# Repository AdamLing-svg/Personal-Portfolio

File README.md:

# About
Third-year Aerospace Engineering student at Toronto Metropolitan University (spacecraft stream), focused on mechanical subsystem design, avionics, and aircraft performance. This repo collects technical reports, design work, and code from coursework and design teams.
---

# Projects

### RC3 2026 — Performance Sizing & Airfoil Selection
*Toronto Metropolitan Aerospace Design (TMAD), Delivery Stream: Jan 2026–Present*

Built a MATLAB performance-sizing model to derive takeoff speed, an 8 m/s stall speed target, 
power requirements, and wing loading. Evaluated 3 candidate airfoils in XFLR5, improving lift coefficient, static margin, and exceeding elevator trim requirements for a design that proceeded to 
manufacturing. I primarily contributed to dry-fitting, assembling, and epoxy-fitting the fuse, nose, wing, 
and landing gear before applying MonoKote. A successful test flight validated performance before a landing 
incident ended eligibility. Below is the final CDR, MATLAB sizing model, design brief, and manufacturing content.  

- [Relevant CDR content and the MATLAB sizing model](./rc3-2026/)
- [Relevant manufacturing content](./rc3manu-2026/)

---

### TMU CanSat — Mission & Mechanical Design
*STEC Initiative Competition: Jan 2026–July 2026*

Developed the mission profile and mass budget, led mechanical system design (mounting, release 
interfaces, hull), and sized the recovery system. Sourced flight hardware (GPS, altimeter, IMU, RF 
module) and developed wiring schematics for manufacturing. Contributed to manufacturing by sourcing components and soldering/wiring avionics for integration with CanSat mounts and software. Below is the final PDR, avionics documentation, and design brief. 

- [Final PDR and schematic documentation](./tmu-cansat/)

---

### Cansat Electrical Sensor Board
*Aug 2026–Sept 2026*

Implements the CanSat electrical onboarding design task: a compact 3.3 V IMU + magnetometer breakout board for real-time deployable-boom orientation sensing. Includes component selection and engineering trade-offs, SPI interface design, KiCad schematic and 4-layer PCB layout, M2 mounting, power/ground strategy, sensor placement considerations, design verification, schematic PDF, Gerber/drill manufacturing files, and supporting design documentation. The design targets ≥400 Hz IMU sampling, ≥100 Hz magnetometer sampling, reliable communication over up to 20 cm, and approximately 20 g launch acceleration.

- [GBR and drill files](./tmu-cansat-gbr-drill/)
- [IMU imported footprint files](./tmu-cansat-IMU/)
- [MAG imported footprint files](./tmu-cansat-MAG/)
- [KiCAD project files and design document](./tmu-cansat-KiCAD-Design/)

---

### Flight Simulator Physics Engine
*Mar 2026–Apr 2026*

Built force and moment modules in Simulink for a six-degree-of-freedom flight simulator that modelled 
aerodynamic forces, thrust, gravity, inertia, and rotational dynamics. Modules were integrated with 
FlightGear visualization and joystick input. Results and process were documented. Below are the completed 
final report, Simulink modules, and project brief. To operate the modules, download all files and run 
RunAircraftModel_AdamForceMomentVersion.m and then run the Simulink (slx) file. 

- [Technical report and project brief](./flight-sim-physics-engine/)
- [Force and moment Simulink modules](./flight-sim-physics-code/)

---

### Battlebot Gearbox Redesign
*Jan 2026–Mar 2026*

Redesigned a spur-gear battle-bot gearbox for cost, alignment, and efficiency while preserving 
compatibility with a competitor unit's ratio, output interface, and mounting geometry. Completed and 
documented research, problem analysis, trade-offs, and the preliminary design. I then evaluated the final two 
preliminary design options to yield a final product decision. 

- [Technical report and CAD parts](./gearbox-project/)

---

### Four-Bar Linkage Walking Mechanism
*Mar 2026 – Apr 2026*

Produced a walking robot that utilizes a linkage mechanism to translate rotational motor by a given 
drivetrain into a walking motion without wheels. Evaluated various designs using MATLAB analysis, manufactured
a physical robot that executed a successful walking motion through laser cutting and 3D printing, and documented 
the design in the form of a technical report. 

- [Technical report and MATLAB 3-bar linkage model](./walking-robot-linkage/)

---

### Stepladder Redesign for Aviation Applications
*Jan 2025 – Apr 2025*

In a team setting, designed a step-ladder solution for aircraft cabins to improve accessibility to overhead compartments and reduce work hazards for flight attendants. Defined design requirements from FAA, OSHA, and ANSI regulations, led the conceptual design through two rejected iterations, and finalized a single-step scissor design with a mechanical locking mechanism.

- [Technical Report](./stepladder/)

---

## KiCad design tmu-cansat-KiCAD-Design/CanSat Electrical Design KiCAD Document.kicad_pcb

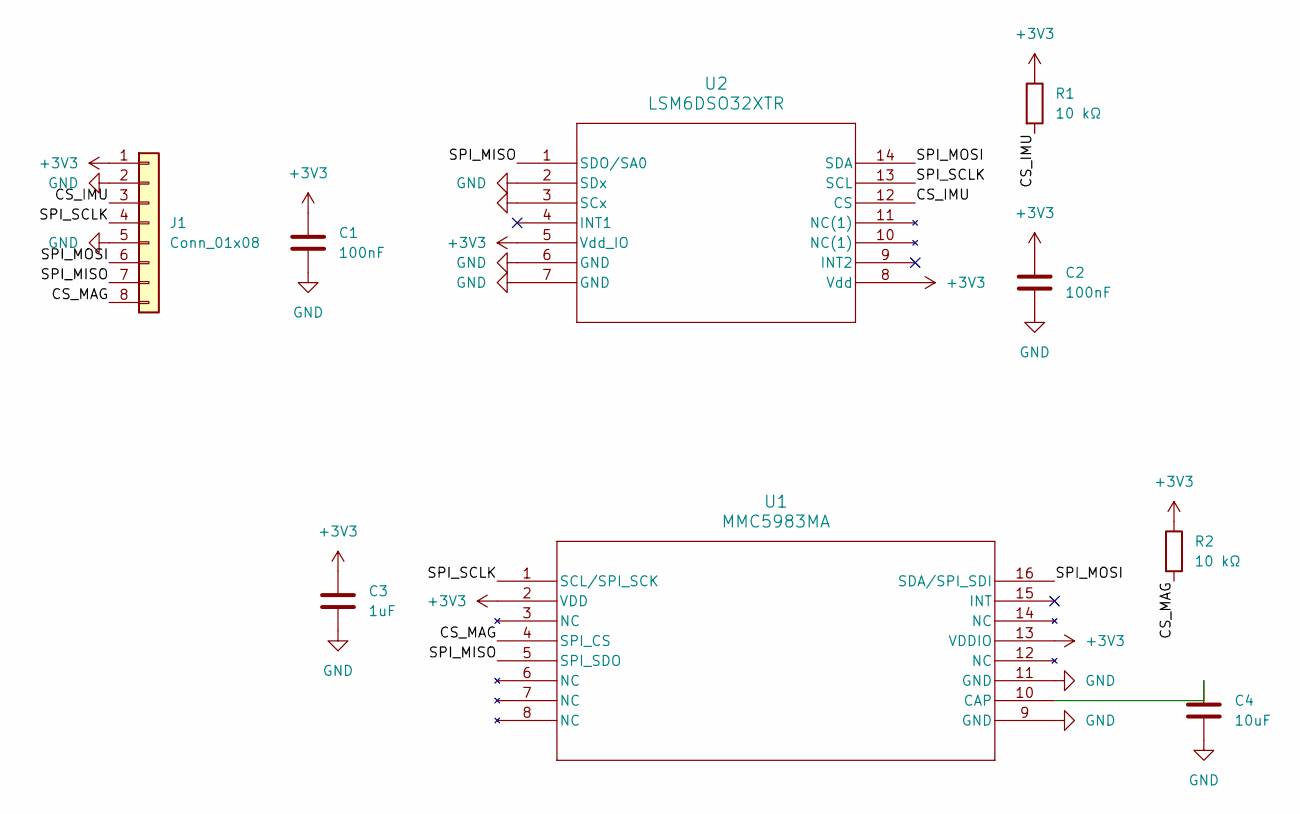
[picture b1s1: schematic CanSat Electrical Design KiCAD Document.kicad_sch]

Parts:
C1, C2: 100nF; C_0603_1608Metric
C3: 1uF; C_0603_1608Metric
C4: 10uF; C_0603_1608Metric
J1: Conn_01x08; JST_GH_SM08B-GHS-TB_1x08-1MP_P1.25mm_Horizontal
R1, R2: 10 kΩ; R_0603_1608Metric
U1: MMC5983MA; MMC5983MA_MEM
U2: LSM6DSO32XTR; LGA_O32XTR_STM

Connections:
+3V3: C1.1, C2.1, C3.1, J1.1, R1.1, R2.1, U1.2 (VDD), U1.13 (VDDIO), U2.5 (Vdd_IO), U2.8 (Vdd)
/CS_IMU: J1.3, R1.2, U2.12 (CS)
/CS_MAG: J1.8, R2.2, U1.4 (SPI_CS)
/SPI_MISO: J1.7, U1.5 (SPI_SDO), U2.1 (SDO/SA0)
/SPI_MOSI: J1.6, U1.16 (SDA/SPI_SDI), U2.14 (SDA)
/SPI_SCLK: J1.4, U1.1 (SCL/SPI_SCK), U2.13 (SCL)
GND: C1.2, C2.2, C3.2, C4.2, J1.2, J1.5, U1.9 (GND), U1.11 (GND), U2.2 (SDx), U2.3 (SCx), U2.6 (GND), U2.7 (GND)
unnamed: C4.1, U1.10 (CAP)

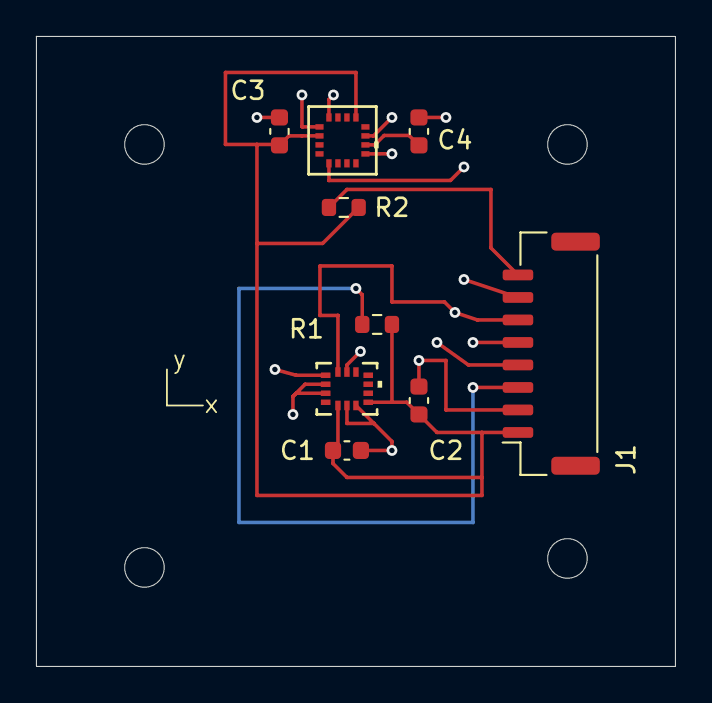
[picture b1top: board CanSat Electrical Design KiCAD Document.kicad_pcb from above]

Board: 4 copper layers, 35.5 x 35.0 mm, 9 parts (0 on the bottom side), 8 nets.
